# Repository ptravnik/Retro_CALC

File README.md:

# Retro_CALC

The ultimate goal is to build a powerful RPN calculator, programmable in BASIC-like language

## The FIRST mockup version:

1. Arduino MEGA 2560
1. [Arduino MEGA SRAM shield](https://hackaday.io/project/21561-arduino-mega-2560-32kb-ram-shield) (my PCB is modified for 56k RAM instead of 32 in the original version)
1. Arduino SD card reader; this version is for Uno, but runs on Mega with pins 10-13 using Soft SPI
1. Piezo speaker on line 9
1. Hardware keyboard on lines A0-A4
1. LCD screen 128x64 pixels on SPI

This code development is abandoned.

## The SECOND mockup version:

1. ESP32 Dev Module
1. Micro SD card reader on VSPI 5, 18, 19, 23
1. Hardware keyboard on lines 25-27 and 32, 33; pin 34 is used for power switch
1. LCD screen 128x64 pixels on HSPI 12-15 
1. Arduino Micro Pro 3.3V, 8 MHz as a "keyboard/mouse injector"

The code is fully ported and tested on the ESP-32 platform. Final version of Keyboard PCB (KBD-2090) has been tested.

## The THIRD mockup version:

1. ESP32 Dev Module
1. Micro SD card reader on VSPI 5, 18, 19, 23
1. Hardware keyboard on lines 25-27 and 32, 33; pin 34 is used for power switch
1. TFT screen 480x320 pixels on HSPI 12-15
1. 2xLiPo batteries (4000 mAh), charger and power management
1. Real-Time Clock based on DS3231 chip
1. Arduino Micro Pro 3.3V, 8 MHz as a "peripheral controller"

This mockup is under development. Both BW LCD and Color TFT are likely to be supported. 

# Build Instructions

## To build for Arduino Mega 2560
1. Tested on Arduino IDE 1.18.10.
1. Install 3 libraries: [U8g2](https://github.com/ptravnik/Retro_CALC/tree/master/U8g2) for the LCD, [SD2](https://github.com/ptravnik/Retro_CALC/tree/master/SD2), and [HWKbd](https://github.com/ptravnik/Retro_CALC/tree/master/HWKbd) for the keyboard. Alternatively just copy the same into the Arduino libraries folder (will not install the examples).
1. Copy the source, [RetroRPN_Arduino](https://github.com/ptravnik/Retro_CALC/tree/master/RetroRPN_Arduino), to any convenient folder and open with Arduino IDE.
1. Select the board as **Arduino Mega or Mega 2560**, processor **ATMega 2560**, compile and upload as usual.

## To build for ESP32 Dev Board
1. Tested on Arduino IDE 1.18.10. and 1.18.12 (VSCode IDE also can be used if Arduino IDE is installed).
1. Install 2 libraries: [U8g2](https://github.com/ptravnik/Retro_CALC/tree/master/U8g2) for the LCD and [HWKbd](https://github.com/ptravnik/Retro_CALC/tree/master/HWKbd) for the keyboard. Alternatively just copy the same into the Arduino libraries folder (will not install the examples).
1. Copy the source, [RetroRPN_ESP32](https://github.com/ptravnik/Retro_CALC/tree/master/RetroRPN_ESP32), to any convenient folder and open with Arduino IDE.
1. Validate which version of hardware keyboard is connected: the production layout uses different h file as the buttons\' position is different from the early mock-up.
1. Select the board as **ESP32 Dev Module**, compile and upload as usual. Dev module requires you to hold **BOOT** down for security reasons; on my module (v 1) this pin is not exposed, so must be done with the button on the module itself. Your board may have this on GPIO 00 pin - wiring to an external button is recommended.

## To build the Keyboard Injector or Peripheral Controller:
1. Tested only with cheap Chinese clones of Sparkfun Pro Micro on Arduino IDE 1.18.10 and 1.18.12.
1. Carefully follow the [install instructions from Sparkfun](https://learn.sparkfun.com/tutorials/pro-micro--fio-v3-hookup-guide/all)
1. Download the [code from github](https://github.com/ptravnik/Retro_CALC/tree/master/Keyboard_Injector_Micro or https://github.com/ptravnik/Retro_CALC/tree/master/MK2090_Peripheral_Controller) 
1. Select the board as **Sparkfun Pro Micro** and the processor as **ATMega 32U4 3.3V, 8MHz** or **ATMega 5.0V 16MHz** version (depending on the one you have); **CAUTION** "Leonardo" may work for 5V / 16 MHz boards, but will surely brick a 3.3V version!
1. Select the board's port
1. Upload to board (shorting Reset to Ground may be required after the interface says "Uploading...")

## Automated testing
1. Place the content of [testing folder](https://github.com/ptravnik/Retro_CALC/tree/master/BASIC_Tests) into the root of the SD card.
1. Insert the SD into the calculator and cycle power button.
1. Upon the calculator wake-up (or new firmware install from the IDE + reboot), issue command **RUN** via Serial Monitor.

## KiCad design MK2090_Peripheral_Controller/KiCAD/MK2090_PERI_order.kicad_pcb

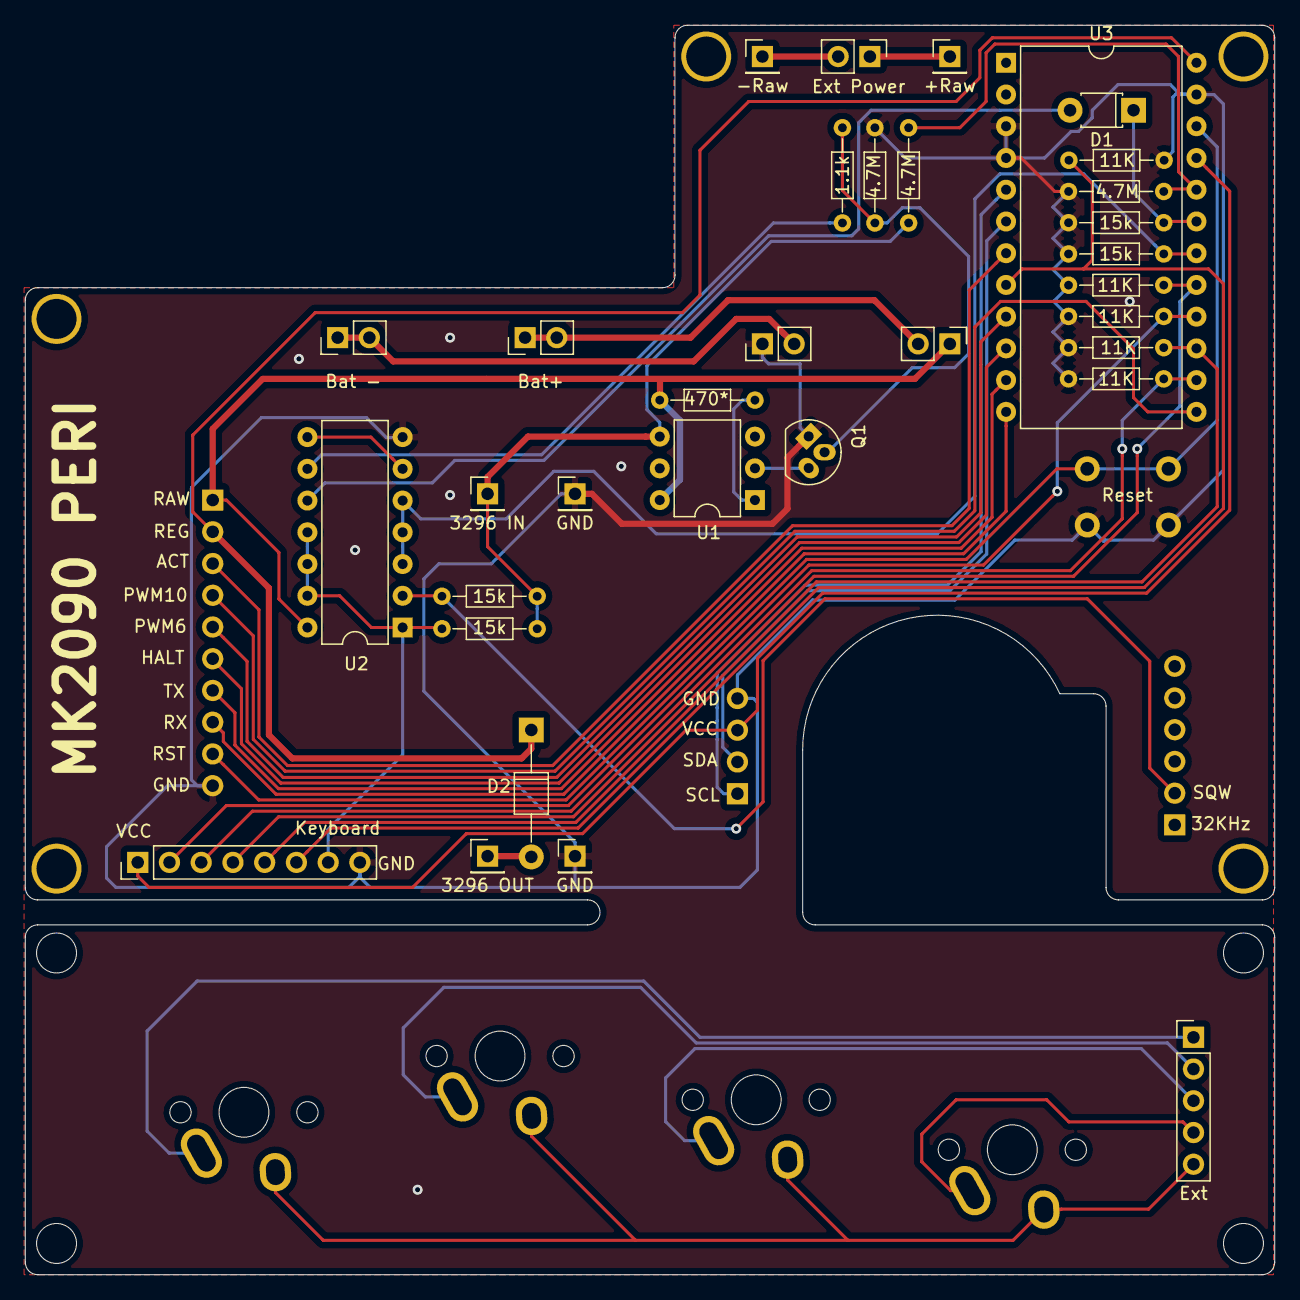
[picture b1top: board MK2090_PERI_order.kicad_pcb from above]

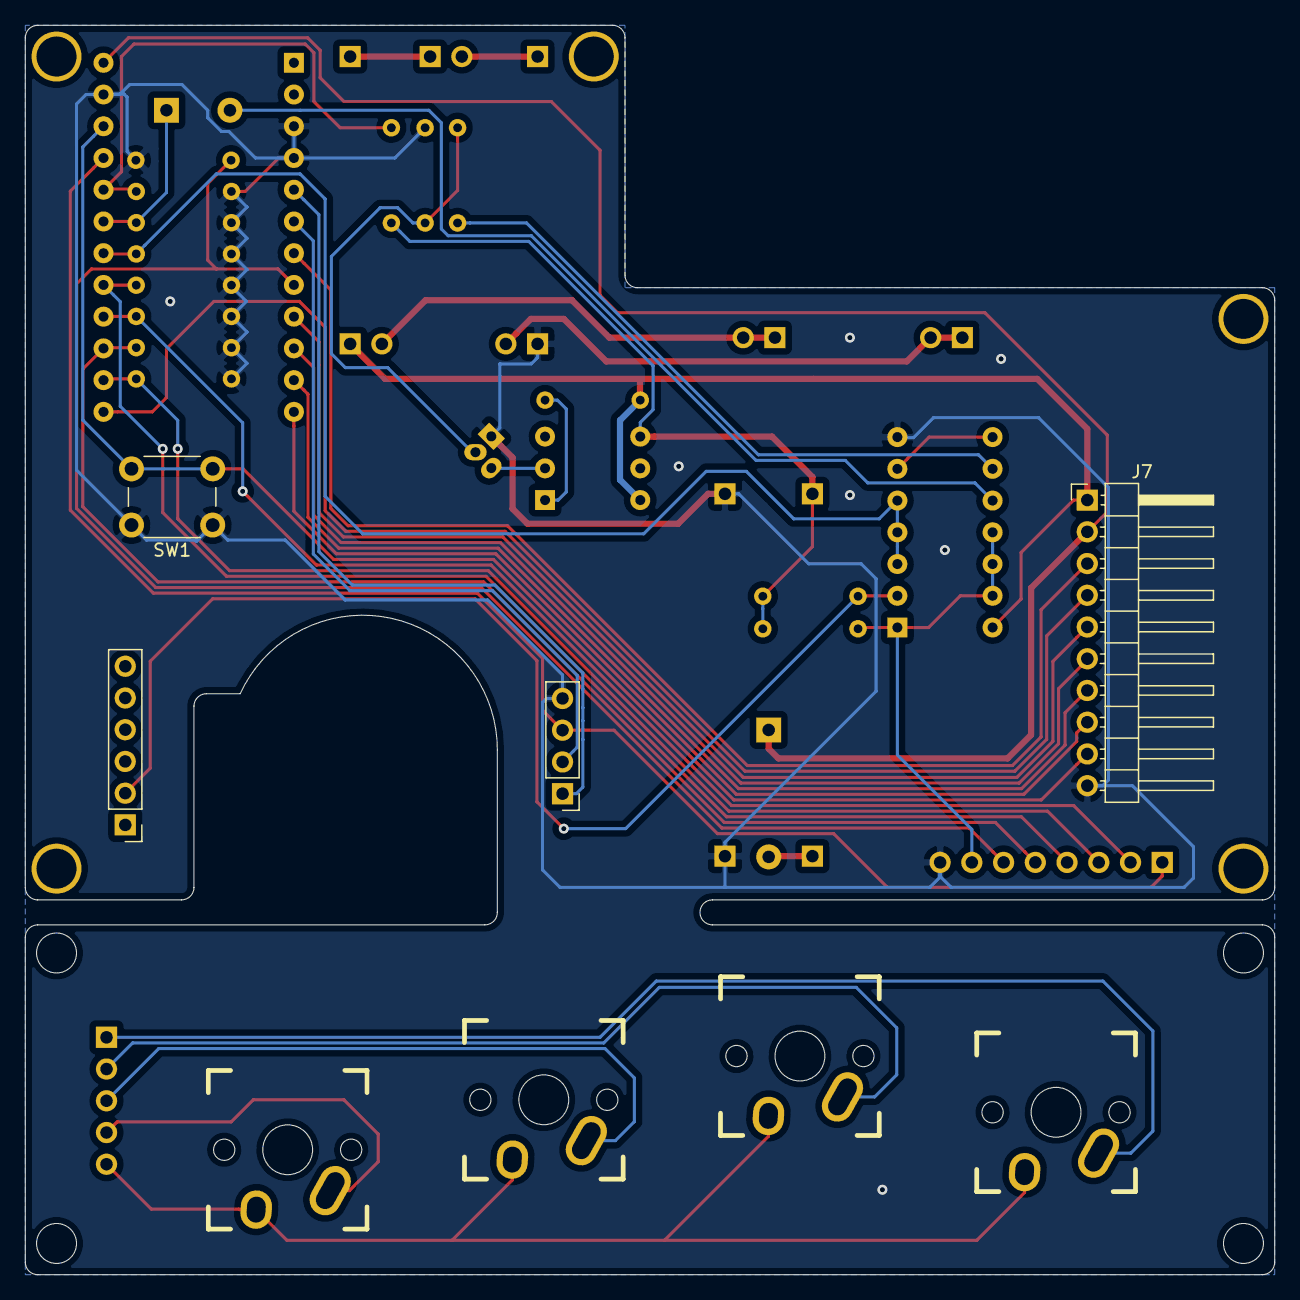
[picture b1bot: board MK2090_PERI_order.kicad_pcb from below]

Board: 2 copper layers, 100.0 x 100.0 mm, 46 parts (8 on the bottom side), 40 nets.

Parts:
D1: 1N5819; D_T-1_P5.08mm_Horizontal
D2: 1N4004; D_T-1_P10.16mm_Horizontal
HOLE_M3, HOLE_M3#2, HOLE_M3#3, HOLE_M3#4, HOLE_M3#5: VAL**; HOLE_M3
J1: +Raw; Pin_Header_Straight_1x01_Pitch2.54mm
J2: -Raw; Pin_Header_Straight_1x01_Pitch2.54mm
J3: 03962a (POS); Pin_Header_Straight_1x02_Pitch2.54mm
J4: 03962a (NEG); Pin_Header_Straight_1x02_Pitch2.54mm
J5: 3296 IN; Pin_Header_Straight_1x01_Pitch2.54mm
J6, J12: GND; Pin_Header_Straight_1x01_Pitch2.54mm
J7: MK2090 PROC; Pin_Header_Angled_1x10_Pitch2.54mm
J8: Keyboard; Pin_Header_Straight_1x08_Pitch2.54mm
J9: RTC; Pin_Header_Straight_1x04_Pitch2.54mm
J10: DS3231; Pin_Header_Straight_1x06_Pitch2.54mm
J11: 3296 OUT; Pin_Header_Straight_1x01_Pitch2.54mm
J13: Ext Power; Pin_Header_Straight_1x02_Pitch2.54mm
J14: Bat+; Pin_Header_Straight_1x02_Pitch2.54mm
J15: Bat -; Pin_Header_Straight_1x02_Pitch2.54mm
J16: Ext; Pin_Header_Straight_1x05_Pitch2.54mm
Q1: 2N7000; TO-92_Molded_Narrow_Oval
R1: 470*; R_Axial_DIN0204_L3.6mm_D1.6mm_P7.62mm_Horizontal
R2, R7, R8: 4.7M; R_Axial_DIN0204_L3.6mm_D1.6mm_P7.62mm_Horizontal
R3: 1.1k; R_Axial_DIN0204_L3.6mm_D1.6mm_P7.62mm_Horizontal
R4, R5, R6, R9: 15k; R_Axial_DIN0204_L3.6mm_D1.6mm_P7.62mm_Horizontal
R10, R11, R12, R13, R14: 11K; R_Axial_DIN0204_L3.6mm_D1.6mm_P7.62mm_Horizontal
SW1: Reset; SW_PUSH_6mm
SW2: E; Mx_Alps_100
SW3: A; Mx_Alps_100
SW4: L; Mx_Alps_100
SW5: Spec; Mx_Alps_100
U1: TLP3544; DIP-6_W7.62mm
U2: 4023; DIP-14_W7.62mm
U3: ProMicro; DIP-24_W15.24mm

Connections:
GND: J4.1, J6.1, J7.10, J8.8, J9.4, J12.1, Q1.1, R2.1, R6.1, R8.1, R9.1, R10.1, R11.1, R12.1, R13.1, R14.1, SW1.1, U2.7, U3.3, U3.4, U3.23
unnamed: D1.1, R9.2, U3.19
unnamed: D1.2, U2.10
unnamed: D2.1, J7.2, U3.24
unnamed: D2.2, J11.1
unnamed: J1.1, J13.1
unnamed: J3.1, J7.1, R1.2, U1.6, U2.14
unnamed: J5.1, R4.2, R5.2, R7.2, U1.4
unnamed: J7.3, U3.7
unnamed: J7.4, U3.13
unnamed: J7.5, U3.9
unnamed: J7.6, U3.10
unnamed: J7.7, U3.11
unnamed: J7.8, U3.12
unnamed: J7.9, SW1.2, U3.22
unnamed: J8.1, J9.3, U3.21
unnamed: J8.2, R11.2, U3.16
unnamed: J8.3, R13.2, U3.14
unnamed: J8.4, R10.2, U3.17
unnamed: J8.5, R12.2, U3.15
unnamed: J8.6, R14.2, U3.8
unnamed: J8.7, R4.1, U2.1, U2.11, U2.12, U2.13
unnamed: J9.1, U3.5
unnamed: J9.2, U3.6
unnamed: J10.2, R5.1, U2.2
unnamed: J2.1, J13.2
unnamed: J3.2, J14.1, J14.2
unnamed: J4.2, J15.1, J15.2
unnamed: J16.1, SW2.1
unnamed: J16.2, SW3.1
unnamed: J16.3, SW4.1
unnamed: J16.4, SW5.1
unnamed: J16.5, SW2.2, SW3.2, SW4.2, SW5.2
unnamed: Q1.2, R2.2, R3.1
unnamed: Q1.3, U1.2
unnamed: R1.1, U1.1
unnamed: R3.2, U2.9
unnamed: R6.2, U2.3, U2.4, U2.5, U3.18
unnamed: R7.1, R8.2, U3.20
unnamed: U2.6, U2.8

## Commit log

2019-10-15 Added the hardware keyboard files
2019-10-16 Separated Encoder class
2019-10-16 Added comments
2019-10-16 Added Cyrillic Phonetic and Classic layouts
2019-10-16 Added code for timer scan
2019-10-16 Added timer scan
2019-10-23 Soft SPI SD card for the development board only
2019-10-23 Added LCD library
2019-10-23 Added files essential for the build
2019-10-23 Fixed pointer
2019-10-23 Separated code into folders
2019-10-23 Created Arduino project
2019-10-23 Changed keyword color
2019-10-24 Minor editing - tabulation
2019-10-24 LCD Terminal added
2019-10-24 Added KiCAD drawings and schematics
2019-10-26 Added codepage for RPN calculator
2019-10-26 RPN stack display operational
2019-10-27 Basic calculator with 4 ops
2019-10-27 basic operations added
2020-02-26 Created ESP32 port for the new hardware
2020-02-26 Added CP1251 codepage
2020-02-26 Typo in the name
2020-03-01 First working prototype
    4 arithmetic operations and full double parsing.
2020-03-01 Refactored generator code
2020-03-01 Modified CP1251 Phonetic layout
2020-03-01 Added Phonetic CP1251 keywords
2020-03-03 Added power management features
2020-03-03 Modified font layout
2020-03-03 Added wiring diagram
2020-03-07 Added stub code for the keyboard injector
2020-03-07 Added wiring diagrams
2020-03-07 Added pin assignments
2020-03-07 Hardware update after Pro Micro 3.3V version
2020-03-08 First working version
2020-03-08 Minor formattng changes
2020-03-08 Minor formatting
2020-03-09 Tested and refactored serial comms
2020-03-09 Debugged serial comms
2020-03-09 Preprocessor tweaks for ESP32
2020-03-10 Touched up library properties
2020-03-11 Added keyboard and mouse injection feature
2020-03-11 Fixed a minor bug with mouse middle button
2020-03-16 Parser refactoring
2020-03-16 defs redactored
2020-03-27 Refactored parser
2020-03-27 Added math functions
2020-03-28 Added pictures
2020-03-28 Added macros for trig functions
2020-04-18 Added algebraic parsing
2020-04-19 Added goff2 solver
2020-04-20 Updated Examples
2020-04-20 Added production layout
2020-04-20 Rearranged to folders
2020-04-23 Added interface switch
2020-04-29 Prior to CLI refactor
2020-05-06 Refactor command line out of RPN
2020-05-09 Added CLI switch
2020-05-09 Added shortcuts to CLI, RPN, EDIT,FMAN
2020-05-09 Added lin2() function
2020-05-09 Added LIN2 function
2020-05-14 Separated UI components
2020-05-20 Implemented instant ON
2020-05-24 Implemented variables and Instant On
2020-05-24 Updated messages
2020-05-26 Incremental build prior to Lexer intro
2020-05-26 Moved to src
2020-05-28 Started Lexer implementation
2020-05-28 Lexer implementation
2020-05-29 Added STORE
2020-05-31 Refactored Variables
2020-06-02 Added automatic testing
2020-06-02 Added program storage, rudimentary run, autotest
2020-06-08 Added calculator sho
2020-06-08 Refactored functions
2020-06-08 Modified test file
2020-06-10 Added shortcuts
2020-06-10 Added conversion functions
2020-06-13 Added converter functions
2020-06-13 Test for converters
2020-06-15 Incremental prior to string implementation
2020-06-15 Probability testing
2020-06-17 Code cleanup
2020-06-17 Added factorial and 2D stats
2020-06-19 Added LOAD and SAVE
2020-06-23 Added editor stub and file ops
2020-06-24 Refactored Instant ON
2020-07-08 Bug fixes, eliminate double redraw
2020-07-08 Added shortcuts to production keyboard
2020-11-11 Updated for power management
2020-11-28 Added DS3231 board
2020-11-28 Fixed modification schematics
2020-11-28 Show wire cuts
2020-11-29 Refactored RTC code
2020-12-01 Reduced memory footprint
2020-12-02 Finalized DS3231 code
2020-12-09 Added Piezo and LCD PWM
2020-12-09 Added PCB files
